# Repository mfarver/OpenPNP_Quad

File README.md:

# OpenPNP_Quad

Hardware and software interfaces for modernizing a Quad Pick and place machine to use @OpenPnP with a circa 1994 era Quad pick and place machine.

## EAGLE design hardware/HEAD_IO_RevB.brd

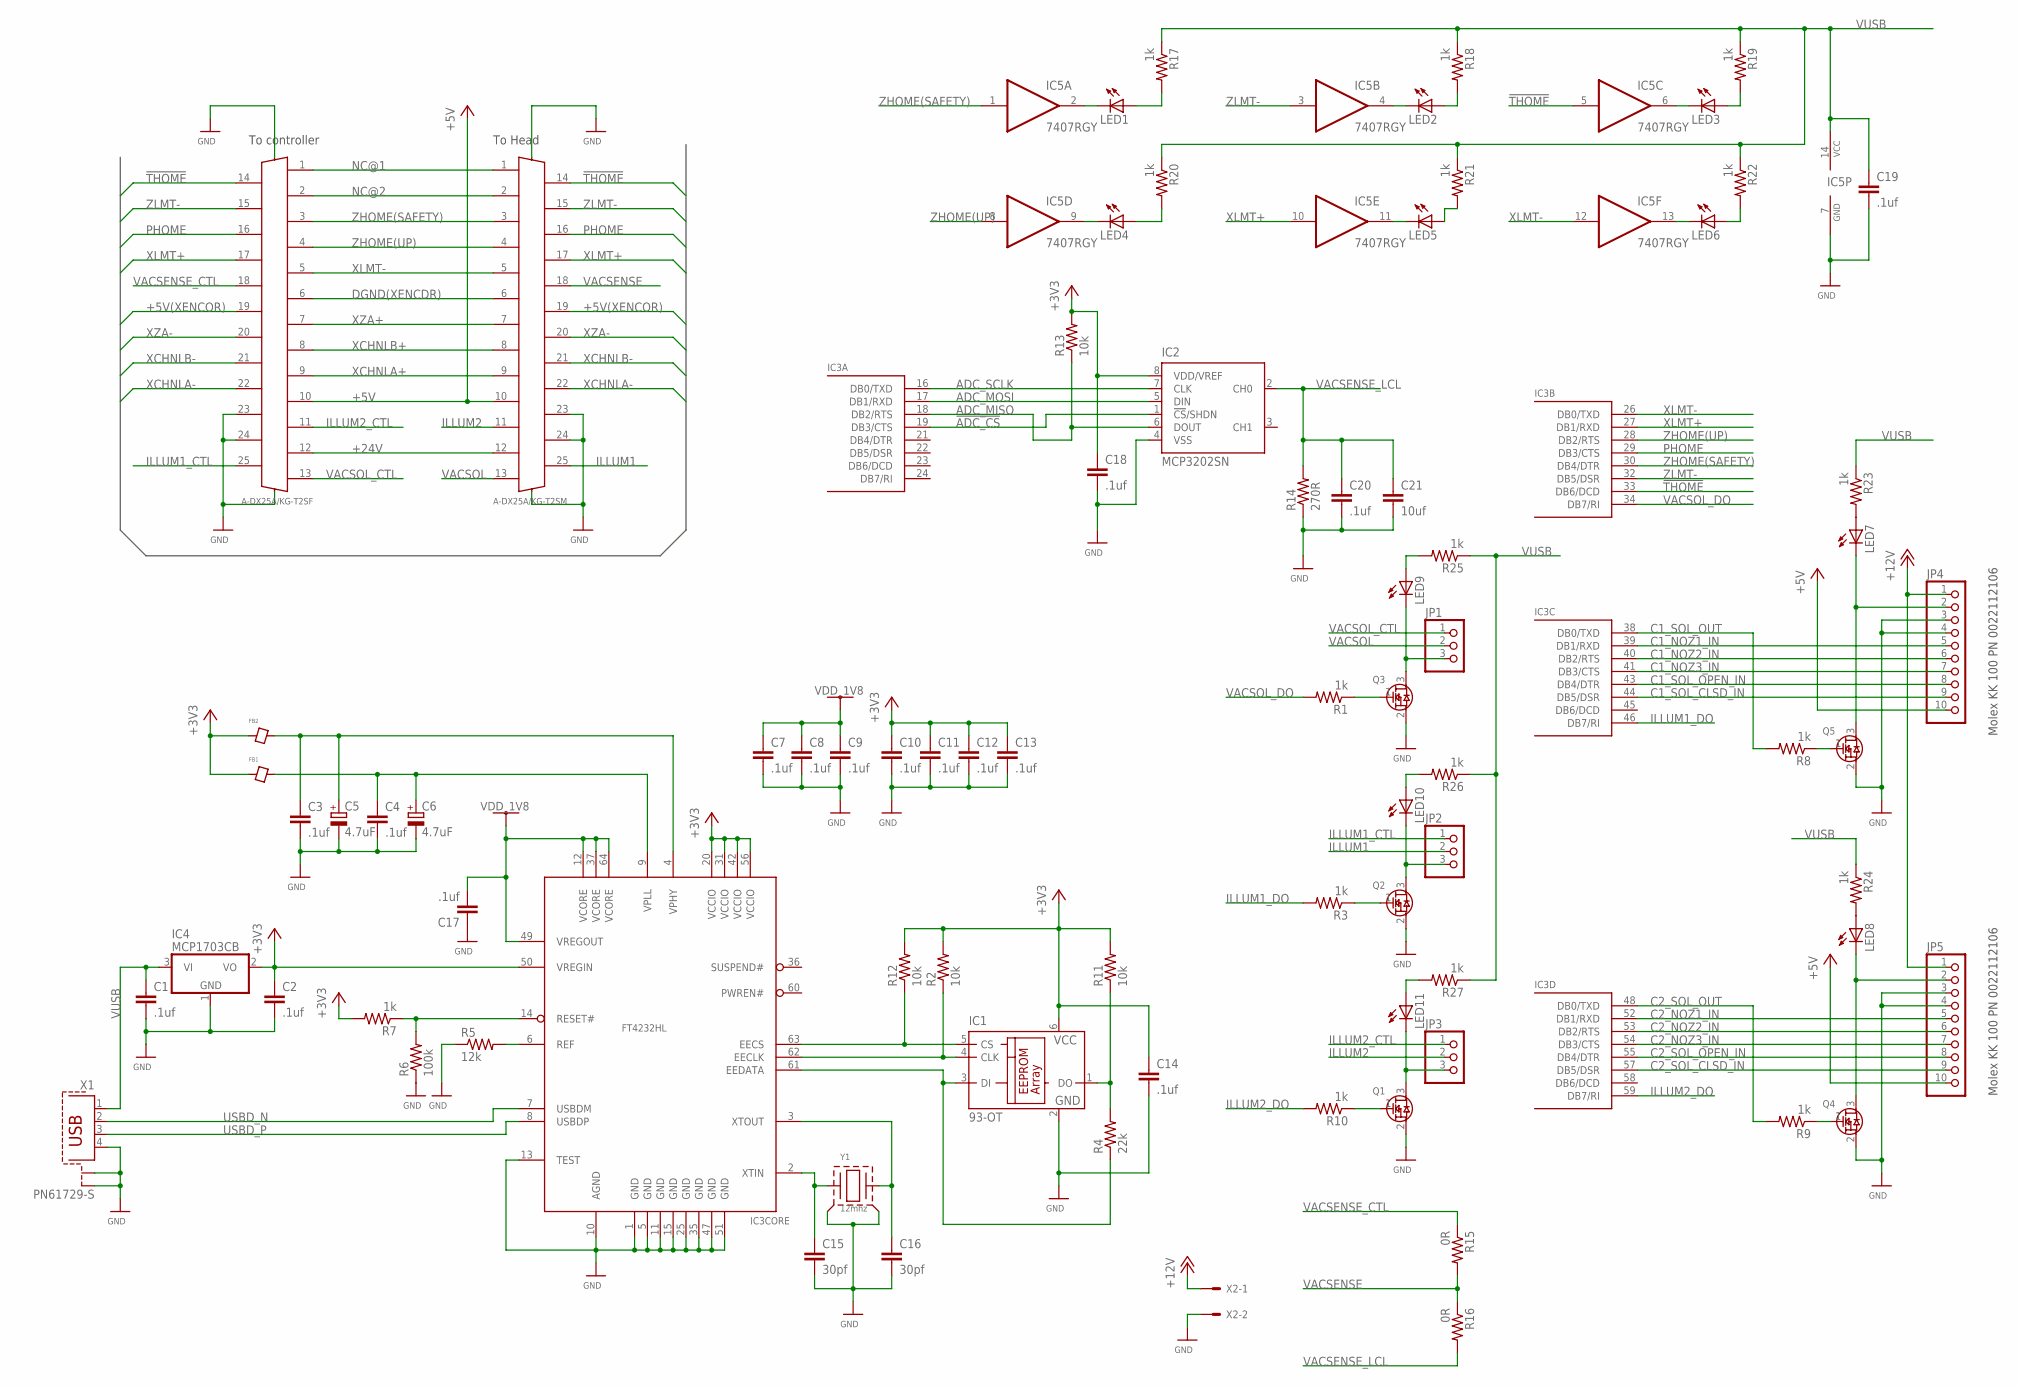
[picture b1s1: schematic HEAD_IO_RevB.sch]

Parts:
C1, C2, C3, C4, C7, C8, C9, C10, C11, C12, C13, C14, C17, C18, C19, C20: .1uf; C0603
C5, C6: 4.7uF; A/3216-18R
C15, C16: 30pf; C0603
C21: 10uf; C0805K
FB1, FB2: FERRITE0603; 0603
IC1: 93-OT; SOT23-6; DIGIKEYPN 93LC46BT-I/OTCT-ND
IC2: MCP3202SN; SO-08
IC3: FT4232HL; LQFP64
IC4: MCP1703CB; SOT23
IC5: 7407RGY; TI_VQFN14
J1: A-DX25A/KG-T2SF; A-DF25A/KG-T2S
J2: A-DX25A/KG-T2SM; A-DS25A/KG-T2S
JP1, JP2, JP3: PINHD-1X3; 1X03
JP4, JP5: PINHD-1X10; 1X10
LED1, LED2, LED3, LED4, LED5, LED6, LED7, LED8, LED9, LED10, LED11: LEDCHIP-LED0603; CHIP-LED0603
Q1, Q2, Q3, Q4, Q5: FDN86246; SOT23C
R1, R3, R7, R8, R9, R10, R17, R18, R19, R20, R21, R22, R23, R24, R25, R26, R27: 1k; R0603
R2, R11, R12, R13: 10k; R0603
R4: 22k; R0603
R5: 12k; R0603
R6: 100k; R0603
R14: 270R; R0603
R15, R16: 0R; R0603
X1: PN61729-S; DIGIKEYPN 609-1039-ND
X2: KK-156-2; DIGIKEYPN WM50008-02-ND
Y1: 12mhz; ABM8G; DIGIKEYPN 535-10261-1-ND

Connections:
!ADC_CS: IC2.1 (!CS!/SHDN), IC3.19 (DB3/CTS)
!RESET: IC3.14 (RESET#), R6.2, R7.1
!THOME: IC3.33 (DB6/DCD), IC5.5 (I), J1.14, J2.14
+3V3: C2.1, C10.1, C11.1, C12.1, C13.1, C14.1, C18.1, FB1.P$1, FB2.P$1, IC1.6 (VCC), IC2.8 (VDD/VREF), IC3.20 (VCCIO), IC3.31 (VCCIO), IC3.42 (VCCIO), IC3.50 (VREGIN), IC3.56 (VCCIO), IC4.2 (VO), R2.2, R7.2, R11.2, R12.2, R13.2
+5V: J1.10, J2.10, JP4.10, JP5.10
+5V(XENCOR): J1.19, J2.19
+12V: JP4.1, JP5.1, X2.1
+24V: J1.12, J2.12
ADC_MISO: IC2.6 (DOUT), IC3.18 (DB2/RTS), R13.1
ADC_MOSI: IC2.5 (DIN), IC3.17 (DB1/RXD)
ADC_SCLK: IC2.7 (CLK), IC3.16 (DB0/TXD)
C1_NOZ1_IN: IC3.39 (DB1/RXD), JP4.5
C1_NOZ2_IN: IC3.40 (DB2/RTS), JP4.6
C1_NOZ3_IN: IC3.41 (DB3/CTS), JP4.7
C1_SOL_CLSD_IN: IC3.44 (DB5/DSR), JP4.9
C1_SOL_OPEN_IN: IC3.43 (DB4/DTR), JP4.8
C1_SOL_OUT: IC3.38 (DB0/TXD), R8.2
C2_NOZ1_IN: IC3.52 (DB1/RXD), JP5.5
C2_NOZ2_IN: IC3.53 (DB2/RTS), JP5.6
C2_NOZ3_IN: IC3.54 (DB3/CTS), JP5.7
C2_SOL_CLSD_IN: IC3.57 (DB5/DSR), JP5.9
C2_SOL_OPEN_IN: IC3.55 (DB4/DTR), JP5.8
C2_SOL_OUT: IC3.48 (DB0/TXD), R9.2
DGND(XENCDR): J1.6, J2.6
GND: C1.2, C2.2, C3.2, C4.2, C5.-, C6.-, C7.2, C8.2, C9.2, C10.2, C11.2, C12.2, C13.2, C14.2, C15.2, C16.2, C17.1, C18.2, C19.2, C20.2, C21.2, IC1.2 (GND), IC2.4 (VSS), IC3.1 (GND), IC3.5 (GND), IC3.10 (AGND), IC3.11 (GND), IC3.13 (TEST), IC3.15 (GND), IC3.25 (GND), IC3.35 (GND), IC3.47 (GND), IC3.51 (GND), IC4.1 (GND), IC5.7 (GND), J1.23, J1.24, J1.SHLD@1 (SHLD), J1.SHLD@2 (SHLD), J2.23, J2.24, J2.SHLD@1 (SHLD), J2.SHLD@2 (SHLD), JP4.3, JP4.4, JP5.3, JP5.4, Q1.2 (S), Q2.2 (S), Q3.2 (S), Q4.2 (S), Q5.2 (S), R5.1, R6.1, R14.1, X1.4, X1.S1, X1.S2, X2.2, Y1.2 (GND), Y1.4 (GND)
ILLUM1: J2.25, JP2.2
ILLUM1_CTL: J1.25, JP2.1
ILLUM1_DO: IC3.46 (DB7/RI), R3.2
ILLUM2: J2.11, JP3.2
ILLUM2_CTL: J1.11, JP3.1
ILLUM2_DO: IC3.59 (DB7/RI), R10.2
unnamed: JP1.3, LED9.C, Q3.3 (D)
unnamed: Q3.1 (G), R1.1
unnamed: JP2.3, LED10.C, Q2.3 (D)
unnamed: Q2.1 (G), R3.1
unnamed: JP3.3, LED11.C, Q1.3 (D)
unnamed: Q1.1 (G), R10.1
unnamed: C16.1, IC3.3 (XTOUT), Y1.3
unnamed: IC3.6 (REF), R5.2
unnamed: C3.1, C5.+, FB2.P$2, IC3.4 (VPHY)
unnamed: C15.1, IC3.2 (XTIN), Y1.1
unnamed: IC1.1 (DO), R4.2, R11.1
unnamed: IC5.2 (O), LED1.C
unnamed: IC5.4 (O), LED2.C
unnamed: IC1.5 (CS), IC3.63 (EECS), R12.1
unnamed: IC1.4 (CLK), IC3.62 (EECLK), R2.1
unnamed: IC1.3 (DI), IC3.61 (EEDATA), R4.1
unnamed: IC5.6 (O), LED3.C
unnamed: IC5.9 (O), LED4.C
unnamed: C4.1, C6.+, FB1.P$2, IC3.9 (VPLL)
unnamed: IC5.11 (O), LED5.C
unnamed: IC5.13 (O), LED6.C
unnamed: LED1.A, R17.2
unnamed: LED2.A, R18.2
unnamed: LED3.A, R19.2
unnamed: LED5.A, R21.2
unnamed: LED6.A, R22.2
unnamed: LED4.A, R20.2
unnamed: LED7.A, R23.2
unnamed: LED8.A, R24.2
unnamed: LED11.A, R27.2
unnamed: Q4.1 (G), R9.1
unnamed: Q5.1 (G), R8.1
unnamed: LED9.A, R25.2
unnamed: LED10.A, R26.2
NC@1: J1.1, J2.1
NC@2: J1.2, J2.2
PHOME: IC3.29 (DB3/CTS), J1.16, J2.16
USBD_N: IC3.7 (USBDM), X1.2
USBD_P: IC3.8 (USBDP), X1.3
VAC1_SW: JP4.2, LED7.C, Q5.3 (D)
VAC2_SW: JP5.2, LED8.C, Q4.3 (D)
VACSENSE: J2.18, R15.2, R16.1
VACSENSE_CTL: J1.18, R15.1
VACSENSE_LCL: C20.1, C21.1, IC2.2 (CH0), R14.2, R16.2
VACSOL: J2.13, JP1.2
VACSOL_CTL: J1.13, JP1.1
VACSOL_DO: IC3.34 (DB7/RI), R1.2
VDD_1V8: C7.1, C8.1, C9.1, C17.2, IC3.12 (VCORE), IC3.37 (VCORE), IC3.49 (VREGOUT), IC3.64 (VCORE)
VUSB: C1.1, C19.1, IC4.3 (VI), IC5.14 (VCC), R17.1, R18.1, R19.1, R20.1, R21.1, R22.1, R23.1, R24.1, R25.1, R26.1, R27.1, X1.1
XCHNLA+: J1.9, J2.9
XCHNLA-: J1.22, J2.22
XCHNLB+: J1.8, J2.8
XCHNLB-: J1.21, J2.21
XLMT+: IC3.27 (DB1/RXD), IC5.10 (I), J1.17, J2.17
XLMT-: IC3.26 (DB0/TXD), IC5.12 (I), J1.5, J2.5
XZA+: J1.7, J2.7
XZA-: J1.20, J2.20
ZHOME(SAFETY): IC3.30 (DB4/DTR), IC5.1 (I), J1.3, J2.3
ZHOME(UP): IC3.28 (DB2/RTS), IC5.8 (I), J1.4, J2.4
ZLMT-: IC3.32 (DB5/DSR), IC5.3 (I), J1.15, J2.15

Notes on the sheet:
To controller
To Head
Molex KK 100 PN 0022112106

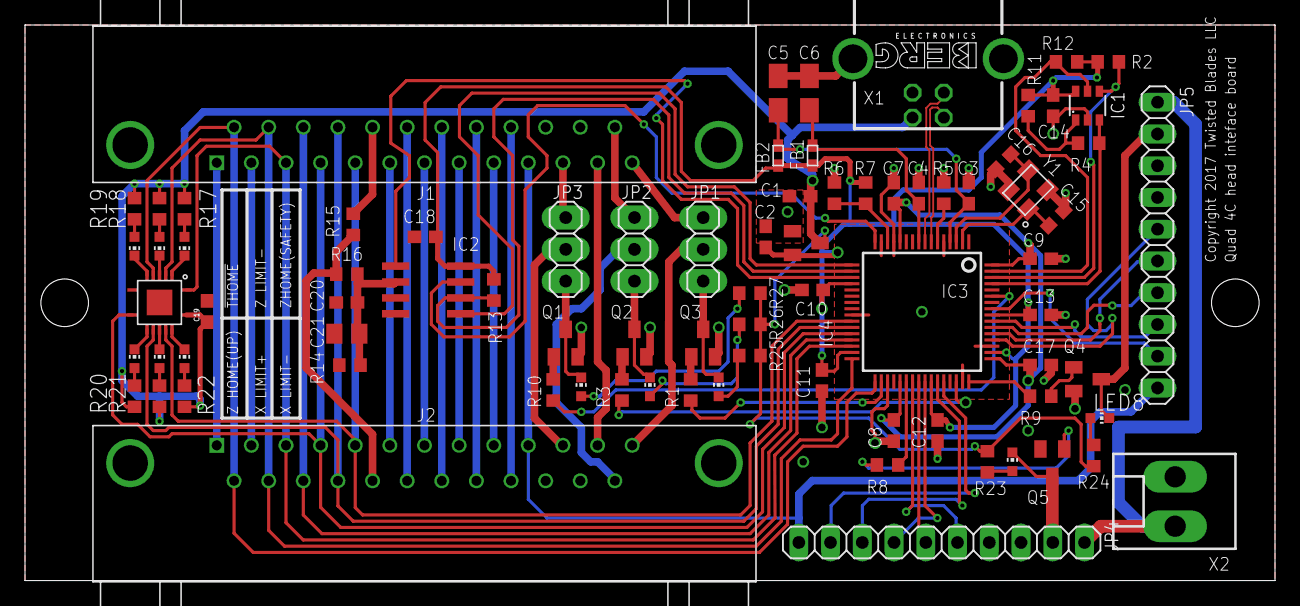
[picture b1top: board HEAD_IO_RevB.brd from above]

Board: 2 copper layers, 100.0 x 44.5 mm, 81 parts (0 on the bottom side), 91 nets.

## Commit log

2022-04-28 Adding hardware design for C/Z axis interface, and documentation of Quad SRX motion controller
2022-05-04 Adding original gcode2srx.py script that was used in the demostration version of the Quad running OpenPNP
2025-08-31 Add files via upload
    add pdf schematic since eagle is going away

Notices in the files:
hardware/HEAD_IO_RevB.brd:
Copyright 2017 Twisted Blades LLC
